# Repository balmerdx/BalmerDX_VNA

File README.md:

# BalmerDX_VNA
Vector Network Analyzer 10 KHz - 180 MHz

[See Wiki documentation for details](https://github.com/balmerdx/BalmerDX_VNA/wiki)

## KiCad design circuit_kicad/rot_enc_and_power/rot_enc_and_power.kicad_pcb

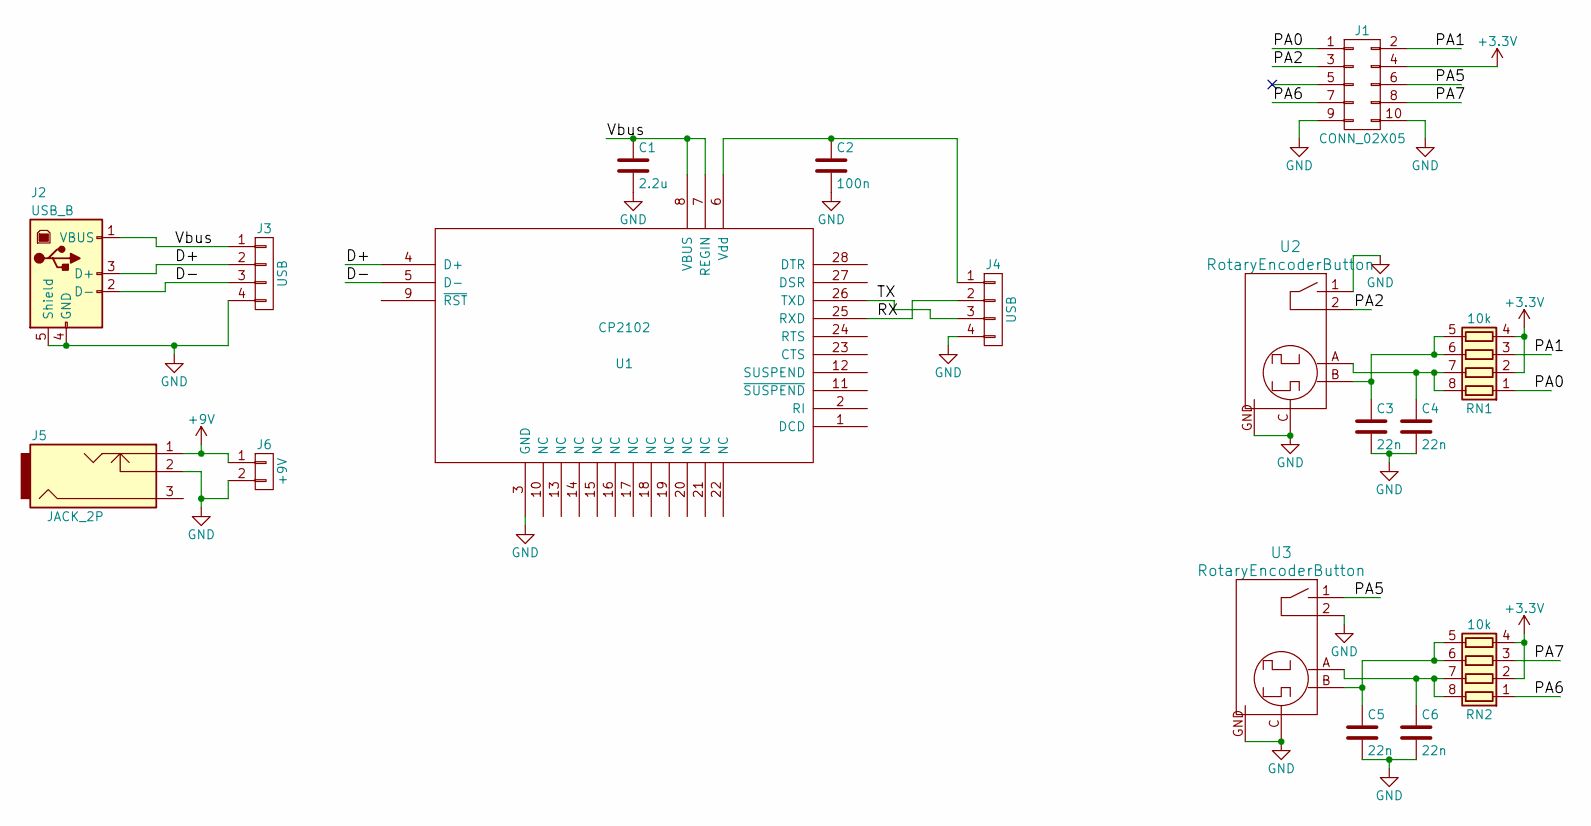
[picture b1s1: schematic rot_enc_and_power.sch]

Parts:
C1: 2.2u; C_0805
C2: 100n; C_0603
C3, C4, C5, C6: 22n; C_0603
J1: CONN_02X05; IDC_10M
J2: USB_B
J3, J4: USB; Pin_Header_Straight_1x04
J5: JACK_2P; JACK_ALIM
J6: +9V; Pin_Header_Straight_1x02
RN1, RN2: 10k; R_Array_Concave_4x0402
U1: CP2102; MLP-28
U2, U3: RotaryEncoderButton; RotEncButton

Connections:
+3V3: J1.4, RN1.2 (R2.1), RN1.4 (R4.1), RN2.2 (R2.1), RN2.4 (R4.1)
+9V: J5.1, J6.1
/D+: J2.3 (D+), J3.2, U1.4 (D+)
/D-: J2.2 (D-), J3.3, U1.5 (D-)
/PA0: J1.1, RN1.1 (R1.1)
/PA1: J1.2, RN1.3 (R3.1)
/PA2: J1.3, U2.2
/PA5: J1.6, U3.1
/PA6: J1.7, RN2.1 (R1.1)
/PA7: J1.8, RN2.3 (R3.1)
/RX: J4.2, U1.25 (RXD)
/TX: J4.3, U1.26 (TXD)
/Vbus: C1.1, J2.1 (VBUS), J3.1, U1.7 (REGIN), U1.8 (VBUS)
GND: C1.2, C2.2, C3.2, C4.2, C5.2, C6.2, J1.9, J1.10, J2.4 (GND), J2.5 (Shield), J3.4, J4.4, J5.2, J6.2, U1.3 (GND), U2.1, U2.C, U2.GND, U3.2, U3.C, U3.GND
unnamed: C2.1, J4.1, U1.6 (Vdd)
unnamed: C3.1, RN1.5 (R4.2), RN1.6 (R3.2), U2.B
unnamed: C4.1, RN1.7 (R2.2), RN1.8 (R1.2), U2.A
unnamed: C5.1, RN2.5 (R4.2), RN2.6 (R3.2), U3.B
unnamed: C6.1, RN2.7 (R2.2), RN2.8 (R1.2), U3.A

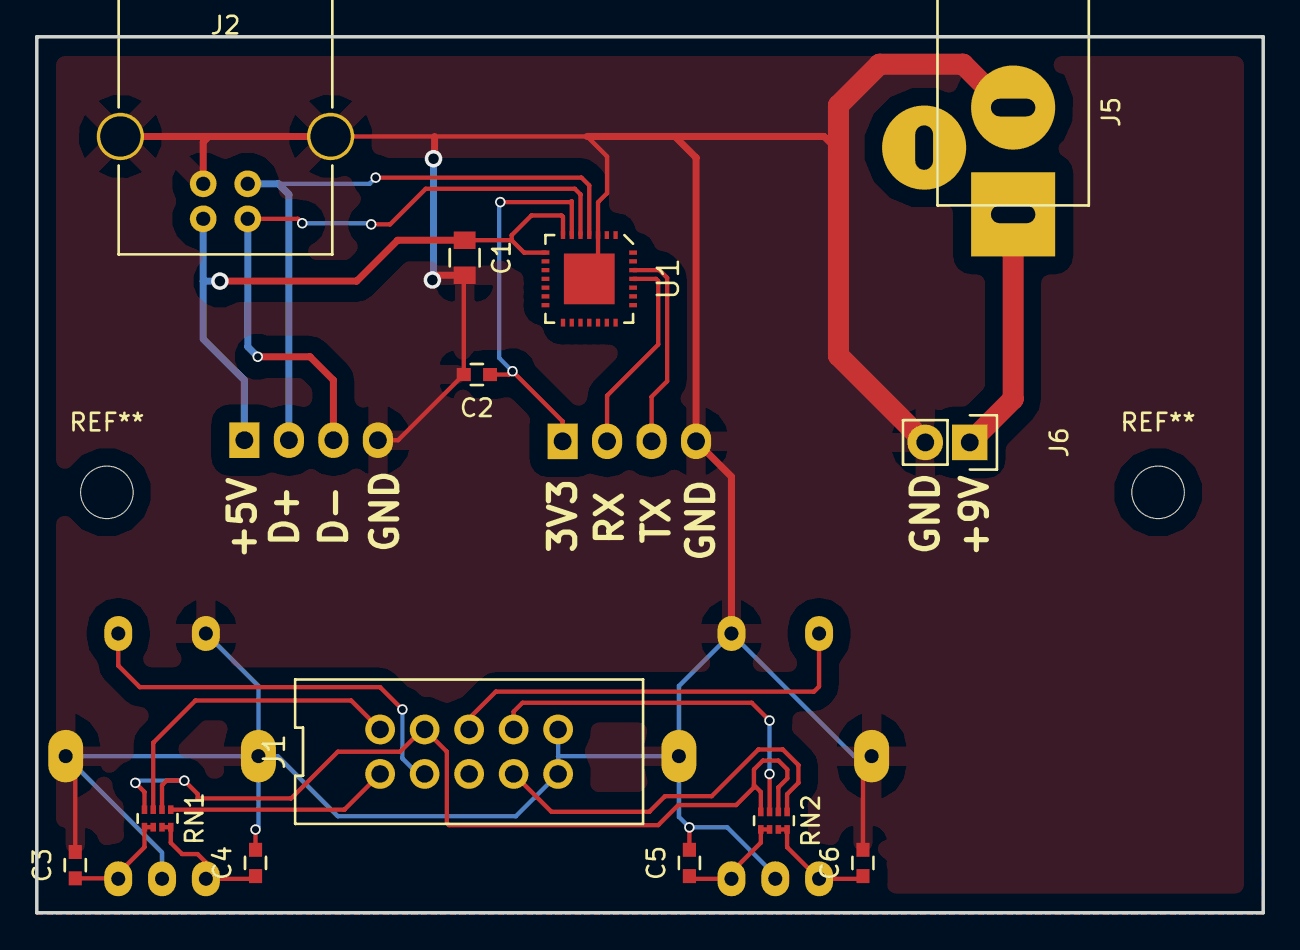
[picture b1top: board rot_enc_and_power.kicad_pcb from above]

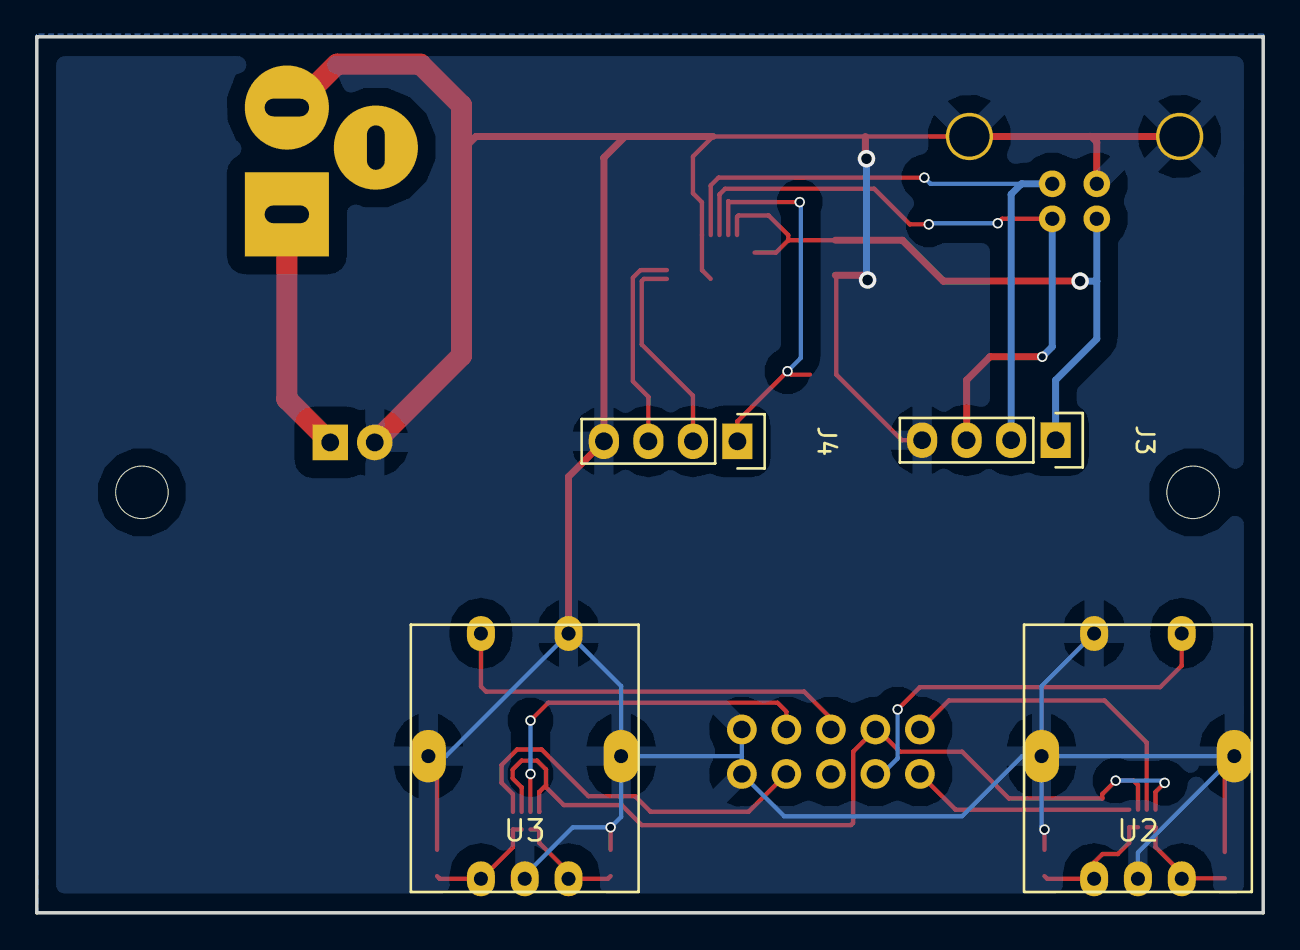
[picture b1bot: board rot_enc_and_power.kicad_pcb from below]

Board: 2 copper layers, 70.0 x 50.0 mm, 17 parts (4 on the bottom side), 19 nets.

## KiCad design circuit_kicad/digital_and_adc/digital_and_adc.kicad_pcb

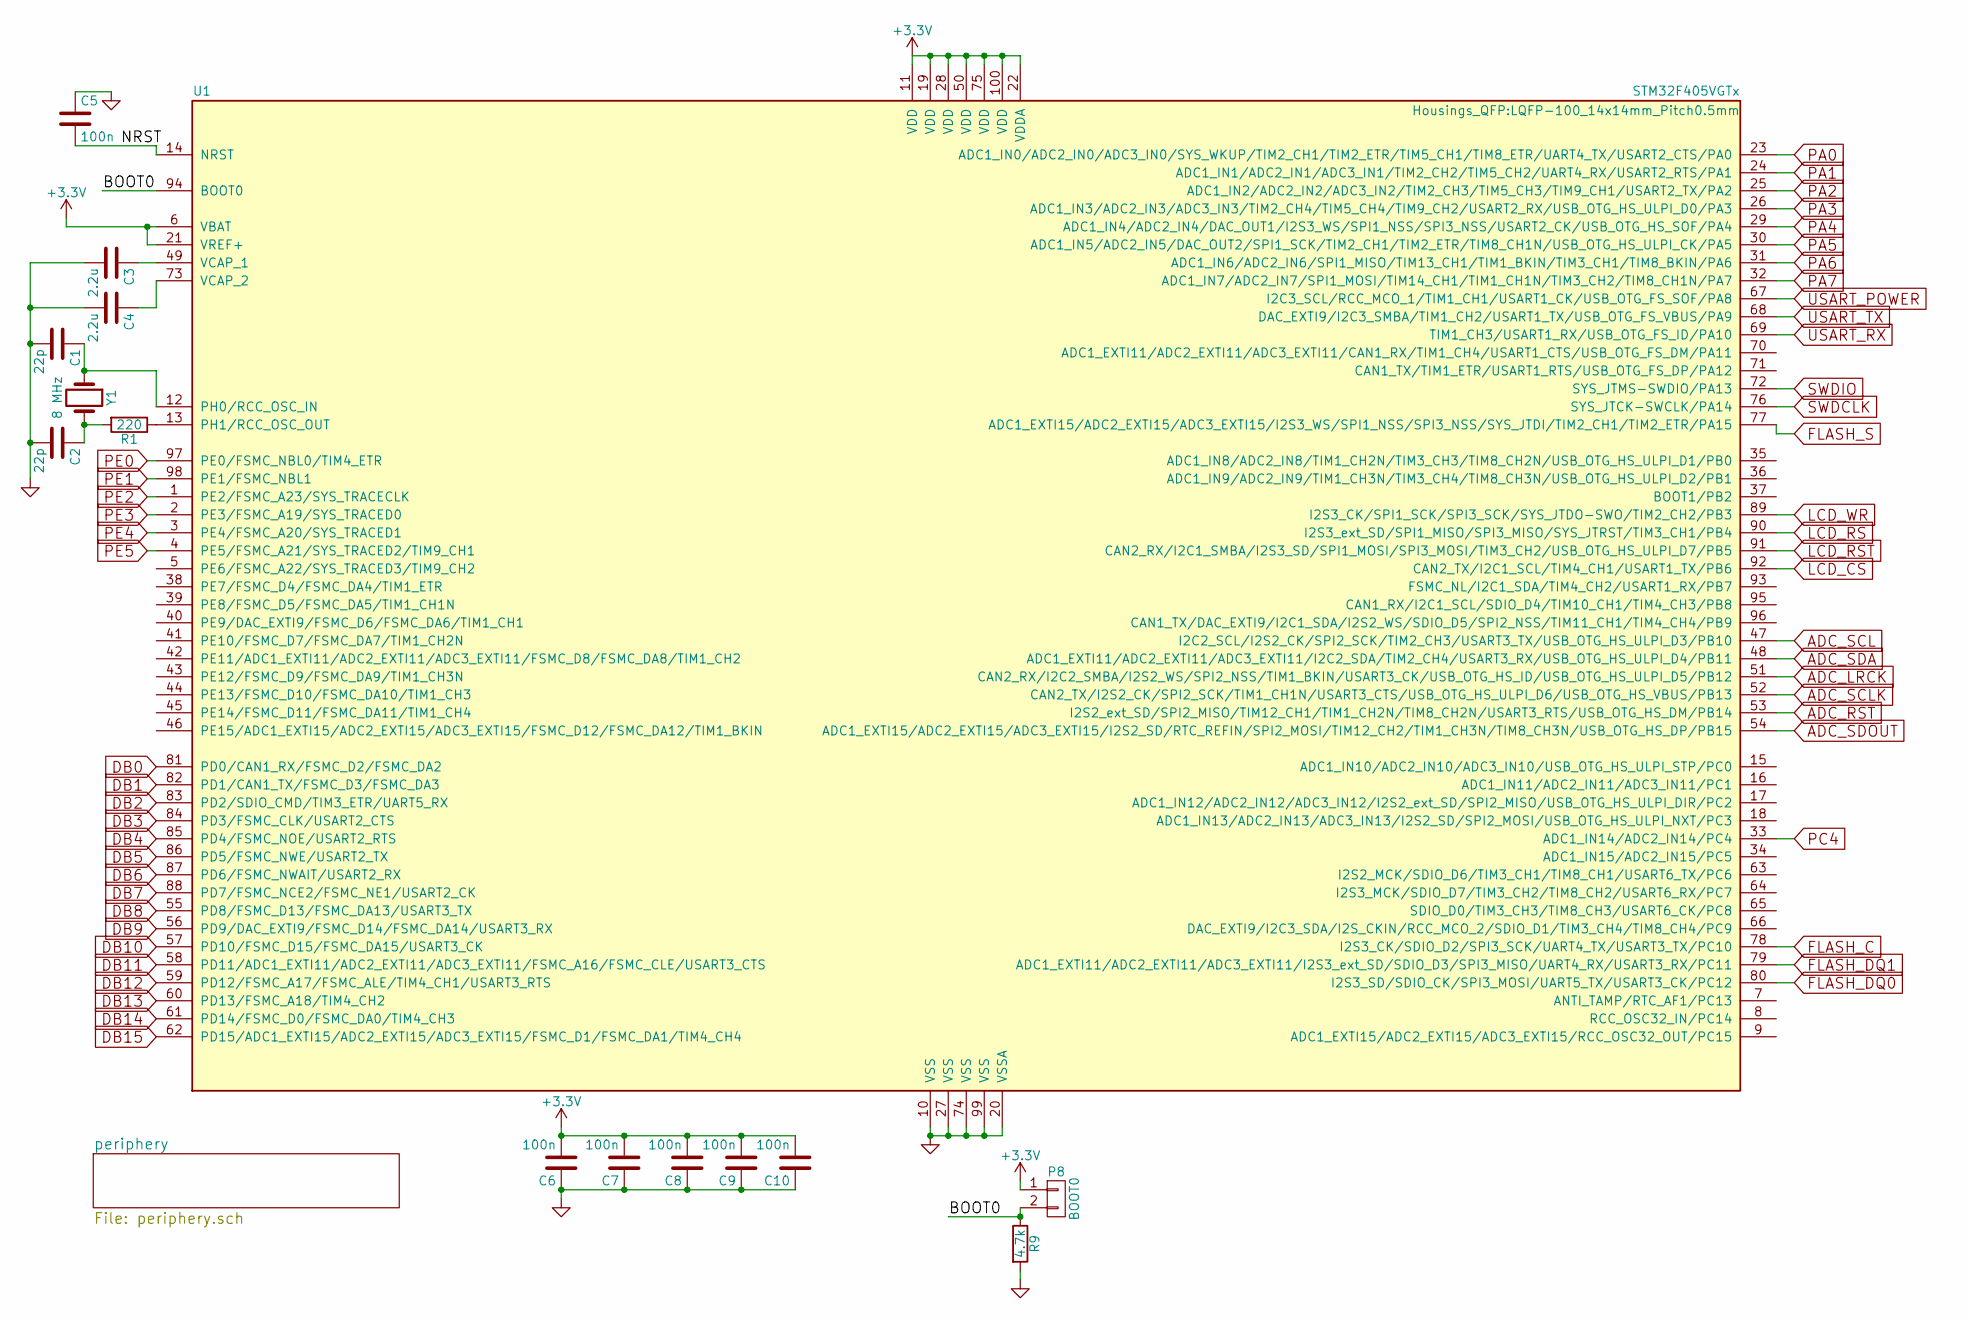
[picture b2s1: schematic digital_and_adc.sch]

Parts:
C1, C2: 22p; C_0603
C3, C4: 2.2u; C_0805
C5, C6, C7, C8, C9, C10: 100n; C_0603
P8: BOOT0; Pin_Header_Straight_1x02
R1: 220; R_0603
R9: 4.7k; R_0603
U1: STM32F405VGTx; LQFP-100_14x14mm_Pitch0.5mm
Y1: 8 MHz; Crystal_HC49-U_Vertical

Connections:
+3V3: C6.2, C7.2, C8.2, C9.2, C10.2, P8.1, U1.6 (VBAT), U1.11 (VDD), U1.19 (VDD), U1.21 (VREF+), U1.22 (VDDA), U1.28 (VDD), U1.50 (VDD), U1.75 (VDD), U1.100 (VDD); also elsewhere on the board
/BOOT0: P8.2, R9.1, U1.94 (BOOT0)
/NRST: C5.2, U1.14 (NRST)
ADC_LRCK: U1.51 (CAN2_RX/I2C2_SMBA/I2S2_WS/SPI2_NSS/TIM1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); also elsewhere on the board
ADC_RST: U1.53 (I2S2_ext_SD/SPI2_MISO/TIM12_CH1/TIM1_CH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); also elsewhere on the board
ADC_SCL: U1.47 (I2C2_SCL/I2S2_CK/SPI2_SCK/TIM2_CH3/USAR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); also elsewhere on the board
ADC_SCLK: U1.52 (CAN2_TX/I2S2_CK/SPI2_SCK/TIM1_CH1N/USAR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); also elsewhere on the board
ADC_SDA: U1.48 (ADC1_EXTI11/ADC2_EXTI11/ADC3_EXTI11/I2C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); also elsewhere on the board
ADC_SDOUT: U1.54 (ADC1_EXTI15/ADC2_EXTI15/ADC3_EXTI15/I2S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); also elsewhere on the board
DB0: U1.81 (PD0/CAN1_RX/FSMC_D2/FSMC_DA2); also elsewhere on the board
DB1: U1.82 (PD1/CAN1_TX/FSMC_D3/FSMC_DA3); also elsewhere on the board
DB2: U1.83 (PD2/SDIO_CMD/TIM3_ETR/UART5_RX); also elsewhere on the board
DB3: U1.84 (PD3/FSMC_CLK/USART2_CTS); also elsewhere on the board
DB4: U1.85 (PD4/FSMC_NOE/USART2_RTS); also elsewhere on the board
DB5: U1.86 (PD5/FSMC_NWE/USART2_TX); also elsewhere on the board
DB6: U1.87 (PD6/FSMC_NWAIT/USART2_RX); also elsewhere on the board
DB7: U1.88 (PD7/FSMC_NCE2/FSMC_NE1/USART2_CK); also elsewhere on the board
DB8: U1.55 (PD8/FSMC_D13/FSMC_DA13/USART3_TX); also elsewhere on the board
DB9: U1.56 (PD9/DAC_EXTI9/FSMC_D14/FSMC_DA14/USART3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); also elsewhere on the board
DB10: U1.57 (PD10/FSMC_D15/FSMC_DA15/USART3_CK); also elsewhere on the board
DB11: U1.58 (PD11/ADC1_EXTI11/ADC2_EXTI11/ADC3_EXTI1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); also elsewhere on the board
DB12: U1.59 (PD12/FSMC_A17/FSMC_ALE/TIM4_CH1/USART3_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); also elsewhere on the board
DB13: U1.60 (PD13/FSMC_A18/TIM4_CH2); also elsewhere on the board
DB14: U1.61 (PD14/FSMC_D0/FSMC_DA0/TIM4_CH3); also elsewhere on the board
DB15: U1.62 (PD15/ADC1_EXTI15/ADC2_EXTI15/ADC3_EXTI1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); also elsewhere on the board
FLASH_C: U1.78 (I2S3_CK/SDIO_D2/SPI3_SCK/UART4_TX/USART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); also elsewhere on the board
FLASH_DQ0: U1.80 (I2S3_SD/SDIO_CK/SPI3_MOSI/UART5_TX/USAR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); also elsewhere on the board
FLASH_DQ1: U1.79 (ADC1_EXTI11/ADC2_EXTI11/ADC3_EXTI11/I2S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); also elsewhere on the board
FLASH_S: U1.77 (ADC1_EXTI15/ADC2_EXTI15/ADC3_EXTI15/I2S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); also elsewhere on the board
GNDD: C1.2, C2.2, C3.2, C4.2, C5.1, C6.1, C7.1, C8.1, C9.1, C10.1, R9.2, U1.10 (VSS), U1.20 (VSSA), U1.27 (VSS), U1.74 (VSS), U1.99 (VSS); also elsewhere on the board
LCD_CS: U1.92 (CAN2_TX/I2C1_SCL/TIM4_CH1/USART1_TX/PB6); also elsewhere on the board
LCD_RS: U1.90 (I2S3_ext_SD/SPI1_MISO/SPI3_MISO/SYS_JTR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); also elsewhere on the board
LCD_RST: U1.91 (CAN2_RX/I2C1_SMBA/I2S3_SD/SPI1_MOSI/SPI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); also elsewhere on the board
LCD_WR: U1.89 (I2S3_CK/SPI1_SCK/SPI3_SCK/SYS_JTDO-SWO/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); also elsewhere on the board
unnamed: C1.1, U1.12 (PH0/RCC_OSC_IN), Y1.1
unnamed: C2.1, R1.2, Y1.2
unnamed: C3.1, U1.49 (VCAP_1)
unnamed: C4.1, U1.73 (VCAP_2)
unnamed: R1.1, U1.13 (PH1/RCC_OSC_OUT)
PA0: U1.23 (ADC1_IN0/ADC2_IN0/ADC3_IN0/SYS_WKUP/TIM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); also elsewhere on the board
PA1: U1.24 (ADC1_IN1/ADC2_IN1/ADC3_IN1/TIM2_CH2/TIM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); also elsewhere on the board
PA2: U1.25 (ADC1_IN2/ADC2_IN2/ADC3_IN2/TIM2_CH3/TIM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); also elsewhere on the board
PA3: U1.26 (ADC1_IN3/ADC2_IN3/ADC3_IN3/TIM2_CH4/TIM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); also elsewhere on the board
PA4: U1.29 (ADC1_IN4/ADC2_IN4/DAC_OUT1/I2S3_WS/SPI1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); also elsewhere on the board
PA5: U1.30 (ADC1_IN5/ADC2_IN5/DAC_OUT2/SPI1_SCK/TIM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); also elsewhere on the board
PA6: U1.31 (ADC1_IN6/ADC2_IN6/SPI1_MISO/TIM13_CH1/T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); also elsewhere on the board
PA7: U1.32 (ADC1_IN7/ADC2_IN7/SPI1_MOSI/TIM14_CH1/T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); also elsewhere on the board
PC4: U1.33 (ADC1_IN14/ADC2_IN14/PC4); also elsewhere on the board
PE0: U1.97 (PE0/FSMC_NBL0/TIM4_ETR); also elsewhere on the board
PE1: U1.98 (PE1/FSMC_NBL1); also elsewhere on the board
PE2: U1.1 (PE2/FSMC_A23/SYS_TRACECLK); also elsewhere on the board
PE3: U1.2 (PE3/FSMC_A19/SYS_TRACED0); also elsewhere on the board
PE4: U1.3 (PE4/FSMC_A20/SYS_TRACED1); also elsewhere on the board
PE5: U1.4 (PE5/FSMC_A21/SYS_TRACED2/TIM9_CH1); also elsewhere on the board
SWDCLK: U1.76 (SYS_JTCK-SWCLK/PA14); also elsewhere on the board
SWDIO: U1.72 (SYS_JTMS-SWDIO/PA13); also elsewhere on the board
USART_POWER: U1.67 (I2C3_SCL/RCC_MCO_1/TIM1_CH1/USART1_CK/U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); also elsewhere on the board
USART_RX: U1.69 (TIM1_CH3/USART1_RX/USB_OTG_FS_ID/PA10); also elsewhere on the board
USART_TX: U1.68 (DAC_EXTI9/I2C3_SMBA/TIM1_CH2/USART1_TX/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); also elsewhere on the board

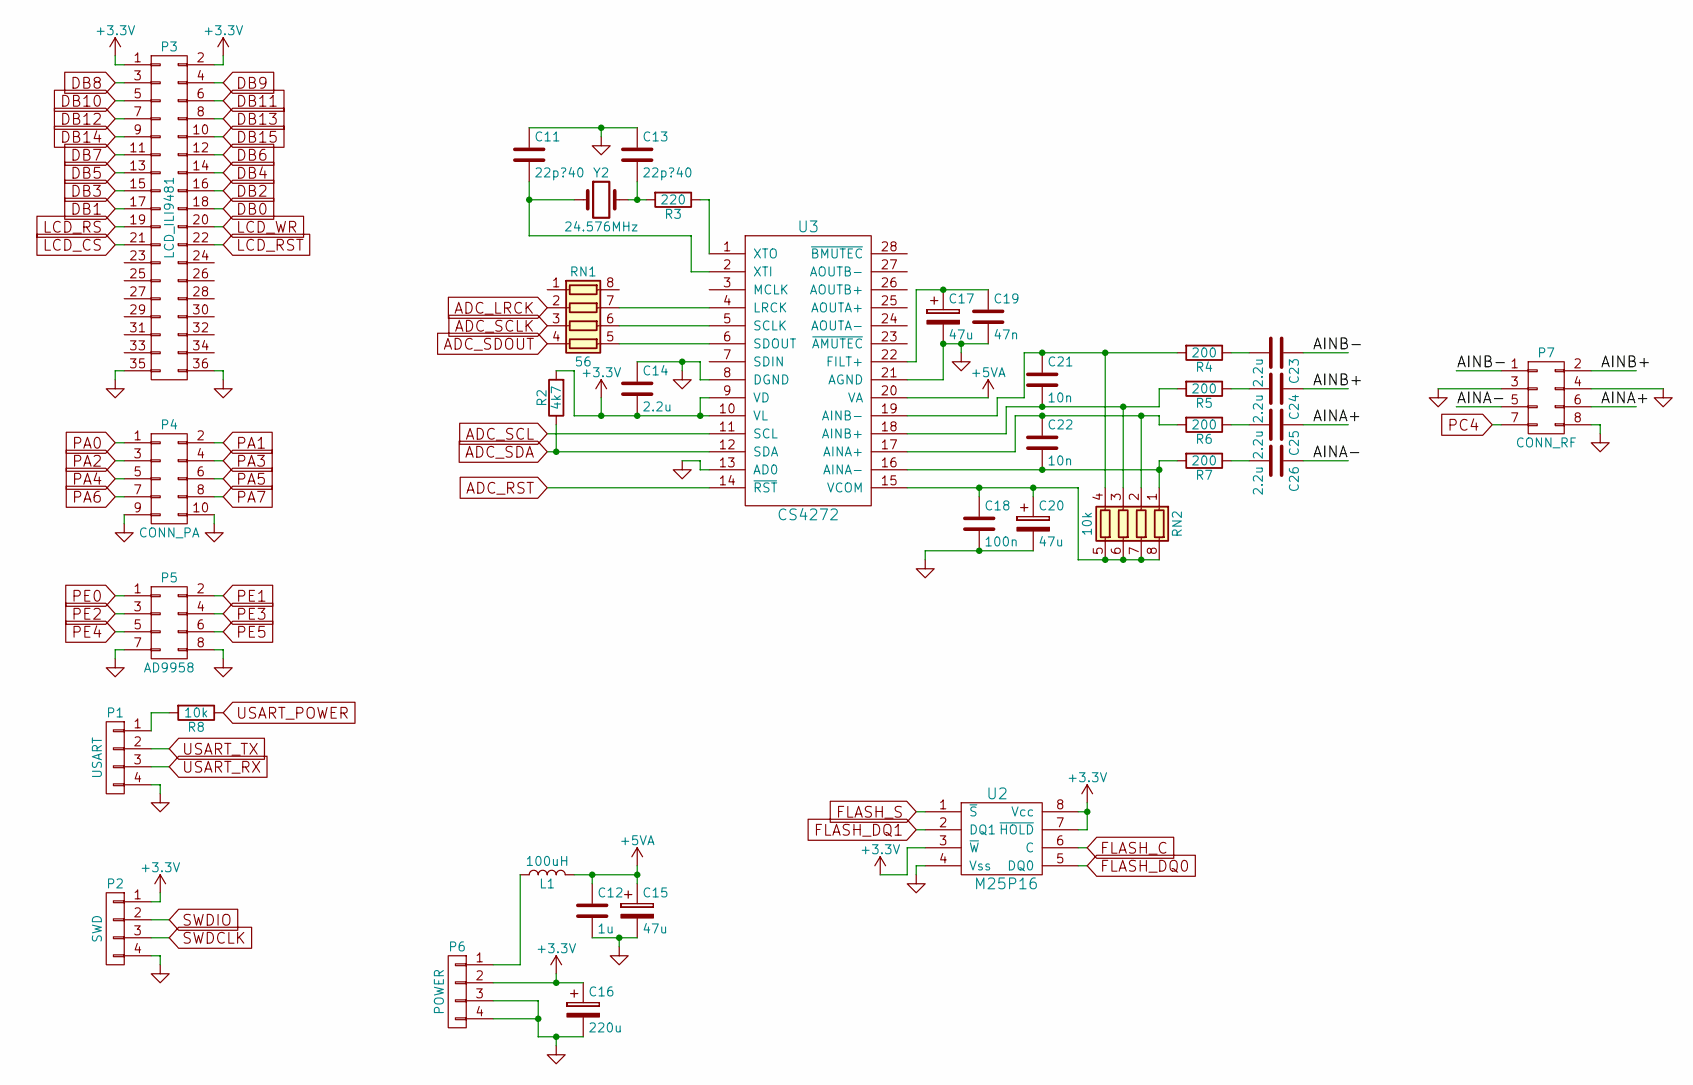
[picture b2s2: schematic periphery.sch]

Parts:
C11, C13: 22p?40; C_0603
C12: 1u; C_0805
C14, C23, C24, C25, C26: 2.2u; C_0805
C15, C17, C20: 47u; TantalC_SizeB_EIA-3528_HandSoldering
C16: 220u; c_elec_6.3x4.5
C18: 100n; C_0805
C19: 47n; C_0805
C21, C22: 10n; C_0603
L1: 100uH; Resistor_Horizontal_RM10mm
P1: USART; Pin_Header_Straight_1x04
P2: SWD; Pin_Header_Straight_1x04
P3: LCD_ILI9481; Pin_Header_Straight_2x18
P4: CONN_PA; Pin_Header_Straight_2x05
P5: AD9958; Pin_Header_Straight_2x04
P6: POWER; Pin_Header_Straight_1x04
P7: CONN_RF; Pin_Header_Straight_2x04
R2: 4k7; R_0603
R3: 220; R_0603
R4, R5, R6, R7: 200; R_0603
R8: 10k; R_0603
RN1: 56; R_Array_Concave_4x0402
RN2: 10k; R_Array_Concave_4x0402
U2: M25P16; SOIC-8-N
U3: CS4272; TSSOP-28_4.4x9.7mm_Pitch0.65mm
Y2: 24.576MHz; Crystal_HC49-U_Vertical

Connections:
+3V3: C14.2, C16.1, P2.1, P3.1, P3.2, P6.2, R2.2, U2.3 (~W), U2.7 (~HOLD), U2.8 (Vcc), U3.9 (VD), U3.10 (VL); also elsewhere on the board
+5VA: C12.1, C15.1, L1.2, U3.20 (VA)
/periphery/AINA+: C25.1, P7.6
/periphery/AINA-: C26.1, P7.5
/periphery/AINB+: C24.1, P7.2
/periphery/AINB-: C23.1, P7.1
ADC_LRCK: RN1.2 (R2.1); also elsewhere on the board
ADC_RST: U3.14 (~RST); also elsewhere on the board
ADC_SCL: U3.11 (SCL); also elsewhere on the board
ADC_SCLK: RN1.3 (R3.1); also elsewhere on the board
ADC_SDA: R2.1, U3.12 (SDA); also elsewhere on the board
ADC_SDOUT: RN1.4 (R4.1); also elsewhere on the board
DB0: P3.18; also elsewhere on the board
DB1: P3.17; also elsewhere on the board
DB2: P3.16; also elsewhere on the board
DB3: P3.15; also elsewhere on the board
DB4: P3.14; also elsewhere on the board
DB5: P3.13; also elsewhere on the board
DB6: P3.12; also elsewhere on the board
DB7: P3.11; also elsewhere on the board
DB8: P3.3; also elsewhere on the board
DB9: P3.4; also elsewhere on the board
DB10: P3.5; also elsewhere on the board
DB11: P3.6; also elsewhere on the board
DB12: P3.7; also elsewhere on the board
DB13: P3.8; also elsewhere on the board
DB14: P3.9; also elsewhere on the board
DB15: P3.10; also elsewhere on the board
FLASH_C: U2.6 (C); also elsewhere on the board
FLASH_DQ0: U2.5 (DQ0); also elsewhere on the board
FLASH_DQ1: U2.2 (DQ1); also elsewhere on the board
FLASH_S: U2.1 (~S); also elsewhere on the board
GNDD: C11.1, C12.2, C13.1, C14.1, C15.2, C16.2, C17.2, C18.2, C19.2, C20.2, P1.4, P2.4, P3.35, P3.36, P4.9, P4.10, P5.7, P5.8, P6.3, P6.4, P7.3, P7.4, P7.8, U2.4 (Vss), U3.8 (DGND), U3.13 (AD0), U3.21 (AGND); also elsewhere on the board
LCD_CS: P3.21; also elsewhere on the board
LCD_RS: P3.19; also elsewhere on the board
LCD_RST: P3.22; also elsewhere on the board
LCD_WR: P3.20; also elsewhere on the board
unnamed: C11.2, U3.2 (XTI), Y2.1
unnamed: C13.2, R3.2, Y2.2
unnamed: C17.1, C19.1, U3.22 (FILT+)
unnamed: C18.1, C20.1, RN2.5 (R4.2), RN2.6 (R3.2), RN2.7 (R2.2), RN2.8 (R1.2), U3.15 (VCOM)
unnamed: C21.1, R4.2, RN2.4 (R4.1), U3.19 (AINB-)
unnamed: C21.2, R5.2, RN2.3 (R3.1), U3.18 (AINB+)
unnamed: C22.1, R6.2, RN2.2 (R2.1), U3.17 (AINA+)
unnamed: C22.2, R7.2, RN2.1 (R1.1), U3.16 (AINA-)
unnamed: C23.2, R4.1
unnamed: C24.2, R5.1
unnamed: C25.2, R6.1
unnamed: C26.2, R7.1
unnamed: L1.1, P6.1
unnamed: P1.1, R8.2
unnamed: R3.1, U3.1 (XTO)
unnamed: RN1.5 (R4.2), U3.6 (SDOUT)
unnamed: RN1.6 (R3.2), U3.5 (SCLK)
unnamed: RN1.7 (R2.2), U3.4 (LRCK)
PA0: P4.1; also elsewhere on the board
PA1: P4.2; also elsewhere on the board
PA2: P4.3; also elsewhere on the board
PA3: P4.4; also elsewhere on the board
PA4: P4.5; also elsewhere on the board
PA5: P4.6; also elsewhere on the board
PA6: P4.7; also elsewhere on the board
PA7: P4.8; also elsewhere on the board
PC4: P7.7; also elsewhere on the board
PE0: P5.1; also elsewhere on the board
PE1: P5.2; also elsewhere on the board
PE2: P5.3; also elsewhere on the board
PE3: P5.4; also elsewhere on the board
PE4: P5.5; also elsewhere on the board
PE5: P5.6; also elsewhere on the board
SWDCLK: P2.3; also elsewhere on the board
SWDIO: P2.2; also elsewhere on the board
USART_POWER: R8.1; also elsewhere on the board
USART_RX: P1.3; also elsewhere on the board
USART_TX: P1.2; also elsewhere on the board

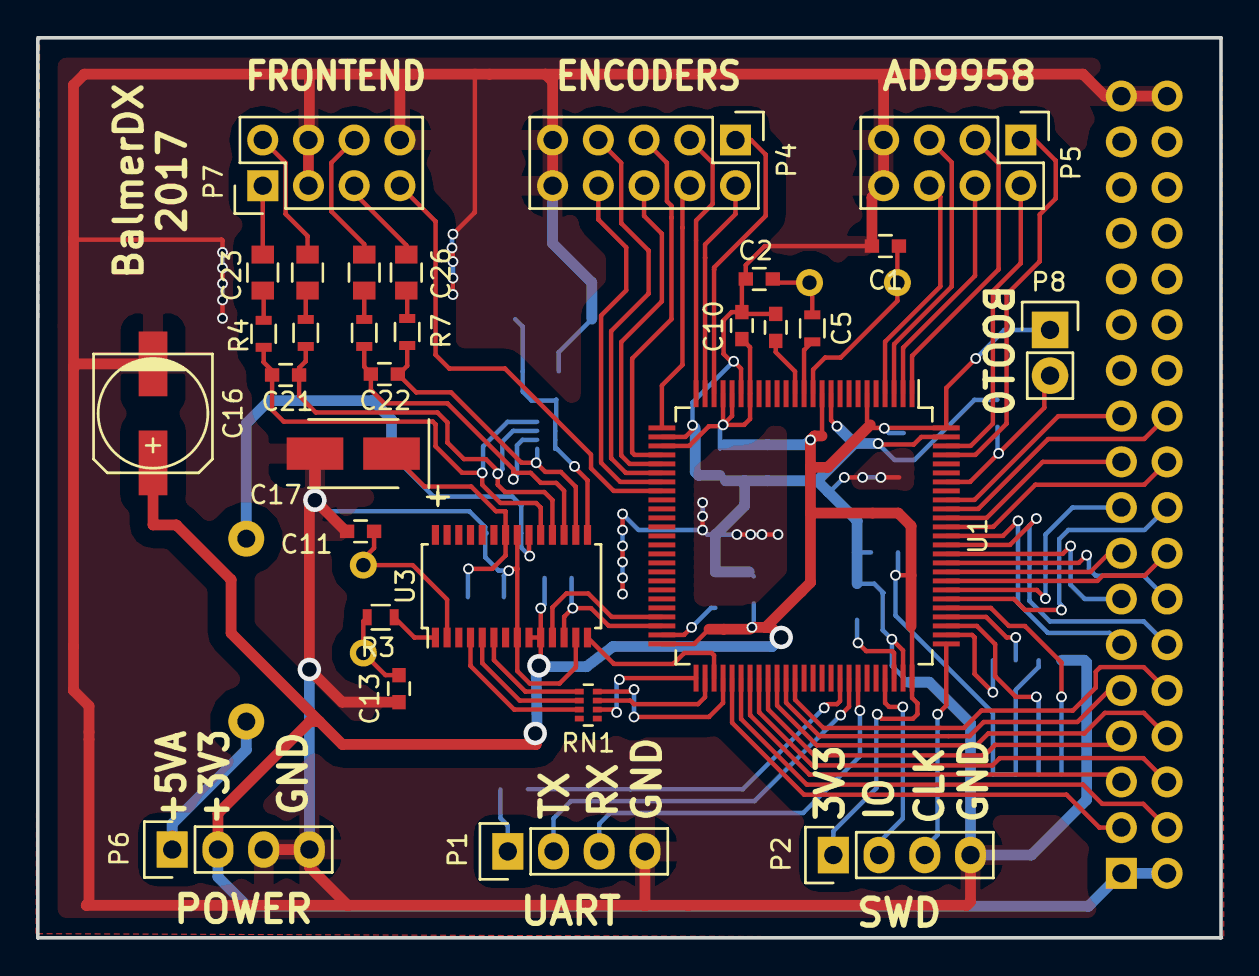
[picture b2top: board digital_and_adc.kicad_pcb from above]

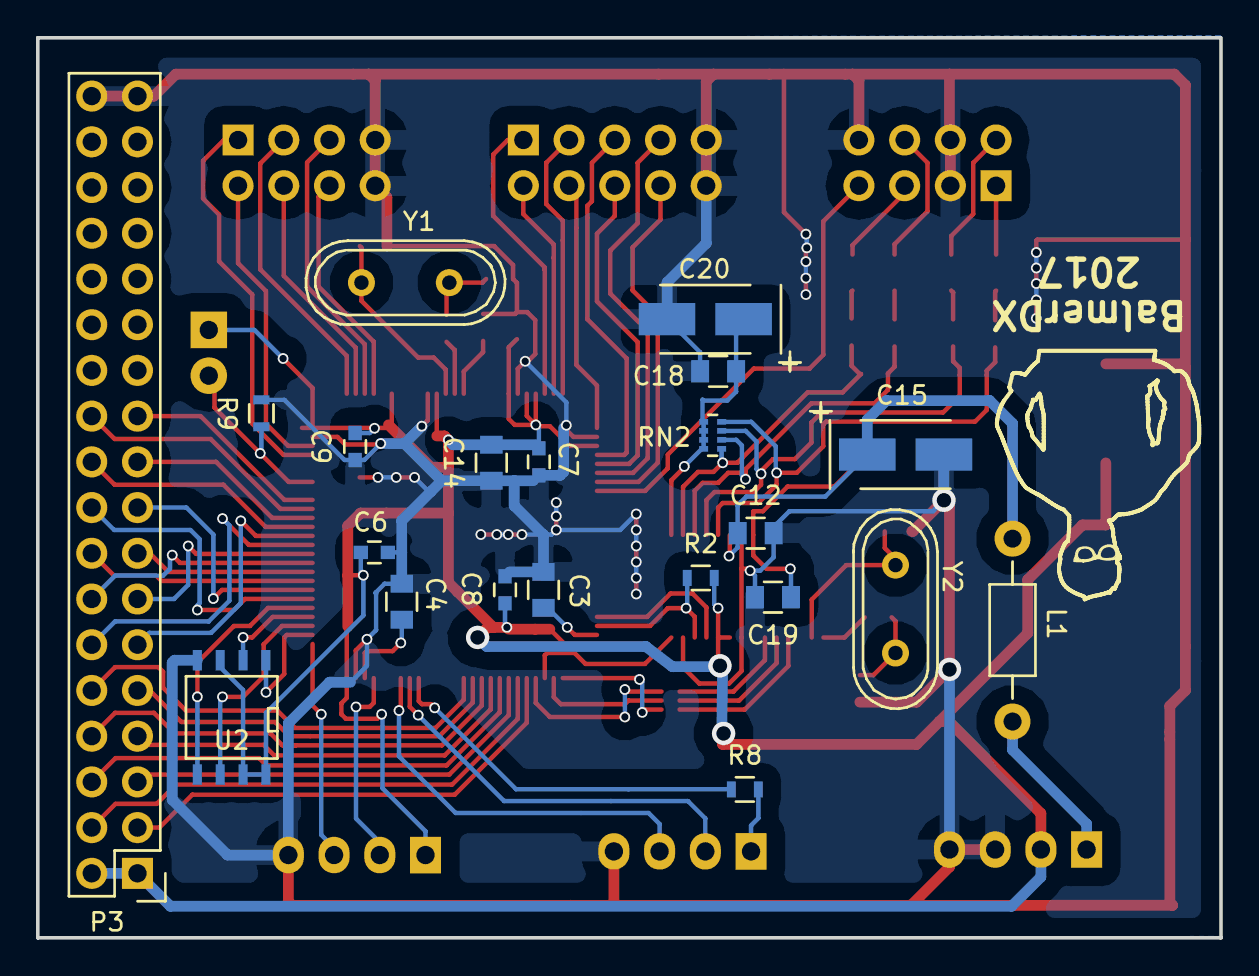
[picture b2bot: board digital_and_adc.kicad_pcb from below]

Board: 2 copper layers, 65.7 x 50.0 mm, 52 parts (22 on the bottom side), 82 nets.

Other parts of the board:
balmer_logo: balmer; balmer_logo

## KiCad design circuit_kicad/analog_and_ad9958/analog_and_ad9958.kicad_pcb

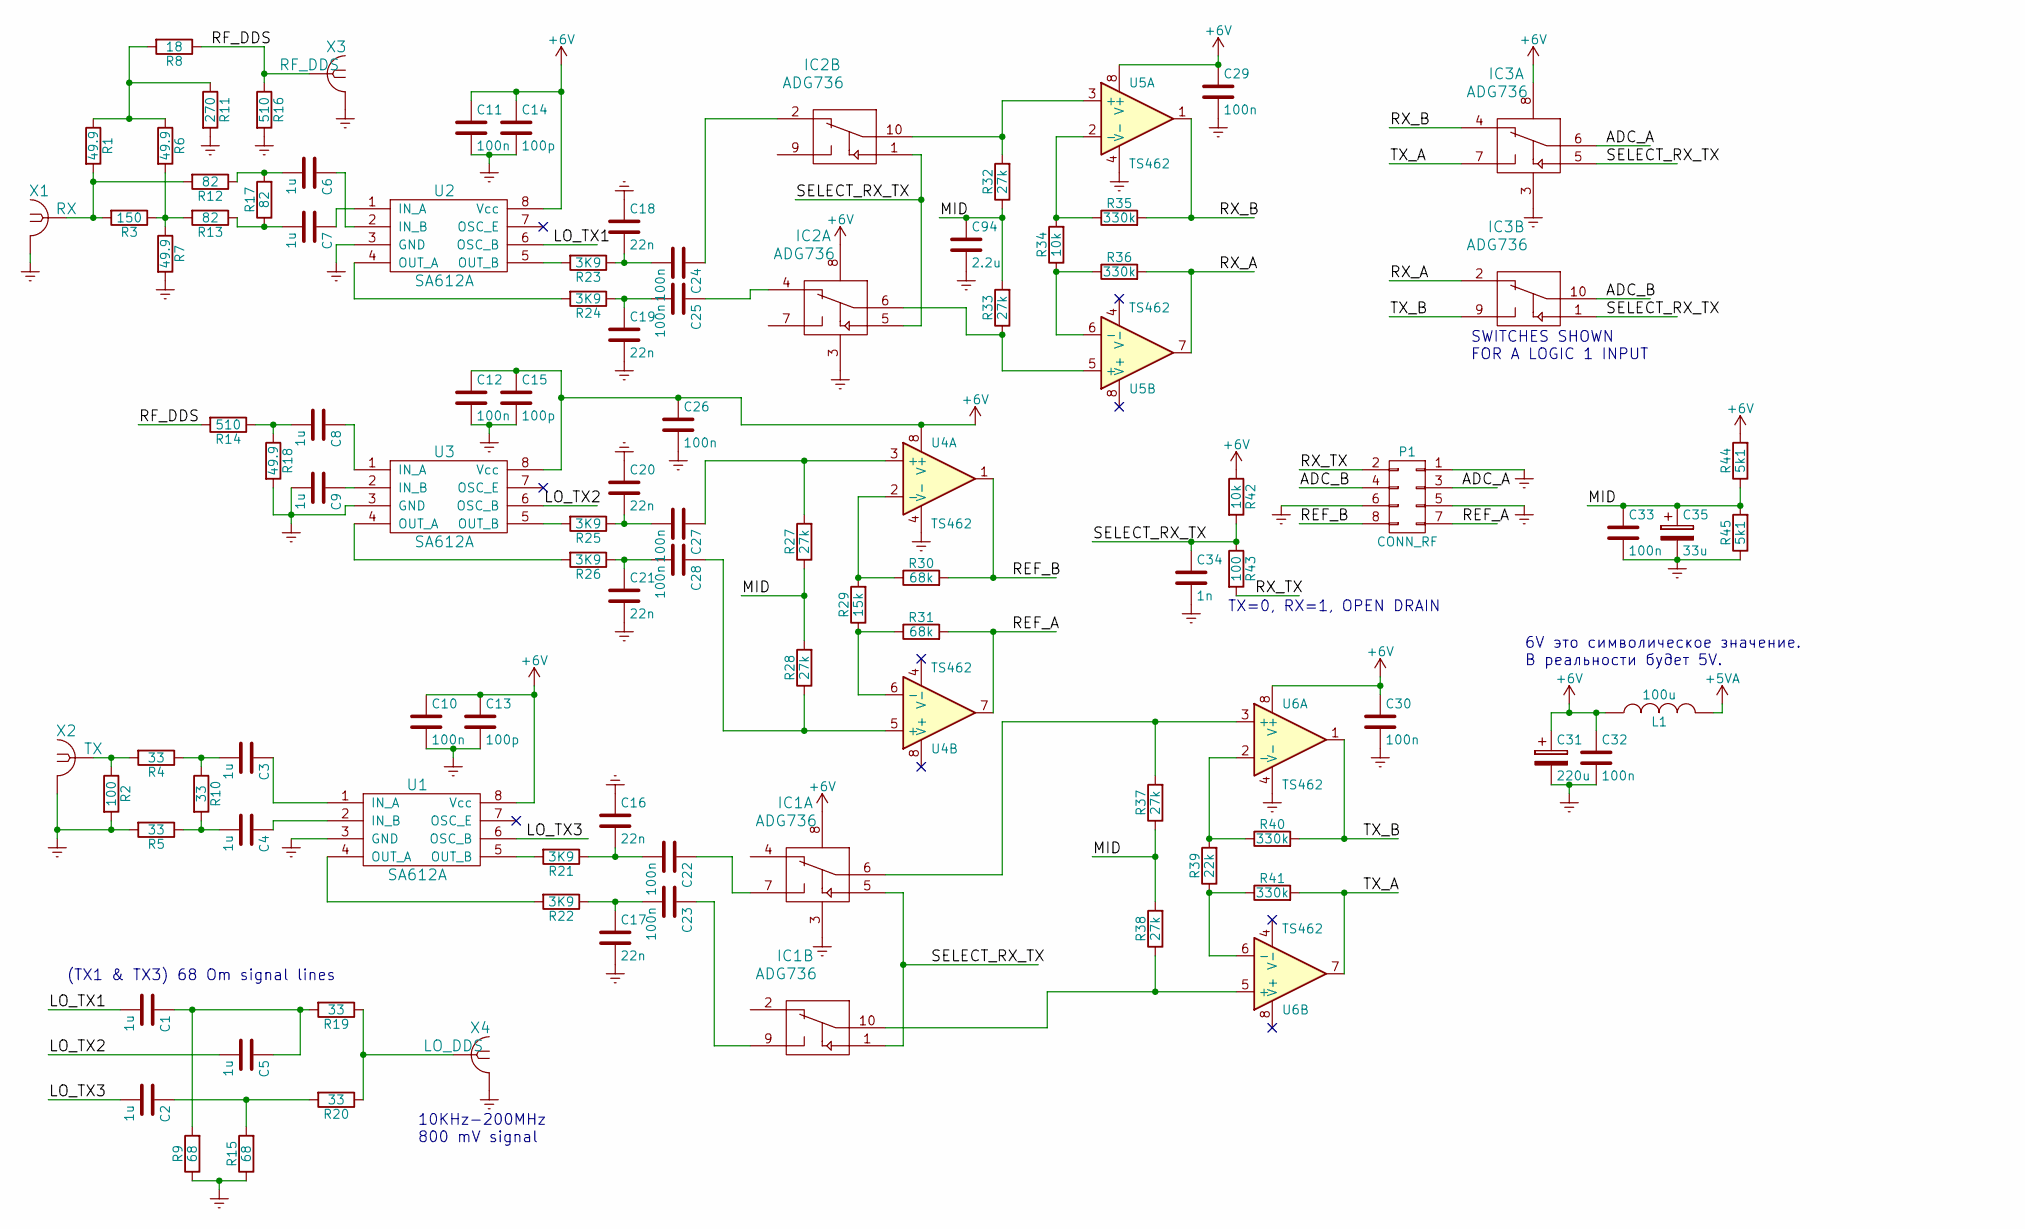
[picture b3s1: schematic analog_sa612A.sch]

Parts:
C1, C2, C3, C4, C5, C6, C7, C8, C9: 1u; C_0603
C10, C11, C12, C22, C23, C24, C25, C26, C27, C28, C29, C30, C32, C33: 100n; C_0603
C13, C14, C15: 100p; C_0603
C16, C17, C18, C19, C20, C21: 22n; C_0603
C31: 220u; c_elec_6.3x4.5
C34: 1n; C_0603
C35: 33u; c_elec_6.3x4.5
C94: 2.2u; C_0805
IC1, IC2, IC3: ADG736; MSOP-10_3x3mm_Pitch0.5mm
L1: 100u; Resistor_Horizontal_RM10mm
P1: CONN_RF; IDC_08M
R1, R6, R7, R18: 49.9; R_0603
R2, R43: 100; R_0603
R3: 150; R_0603
R4, R5, R10: 33; R_0603
R8: 18; R_0603
R9, R15: 68; R_0805
R11: 270; R_0603
R12, R13, R17: 82; R_0603
R14, R16: 510; R_0603
R19, R20: 33; R_0805
R21, R22, R23, R24, R25, R26: 3K9; R_0603
R27, R28, R32, R33, R37, R38: 27k; R_0603
R29: 15k; R_0603
R30, R31: 68k; R_0603
R34, R42: 10k; R_0603
R35, R36, R40, R41: 330k; R_0603
R39: 22k; R_0603
R44, R45: 5k1; R_0603
U1, U2, U3: SA612A; SOIC-8-N
U4, U5, U6: TS462; SOIC-8-N
X1: RX; SMA-NORMAL
X2: TX; SMA-NORMAL
X3: RF_DDS; SMA-NORMAL-MY
X4: LO_DDS; SMA-NORMAL-MY

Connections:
+5VA: L1.2; also elsewhere on the board
+6V: C10.1, C11.1, C12.1, C13.1, C14.1, C15.1, C26.1, C29.1, C30.1, C31.1, C32.1, IC1.8, IC2.8, IC3.8, L1.1, R42.1, R44.2, U1.8 (Vcc), U2.8 (Vcc), U3.8 (Vcc), U4.8 (V+), U5.8 (V+), U6.8 (V+)
/analog_sa612A/ADC_A: IC3.6, P1.3
/analog_sa612A/ADC_B: IC3.10, P1.4
/analog_sa612A/LO_TX1: C1.2, U2.6 (OSC_B)
/analog_sa612A/LO_TX2: C5.2, U3.6 (OSC_B)
/analog_sa612A/LO_TX3: C2.2, U1.6 (OSC_B)
/analog_sa612A/MID: C33.1, C35.1, C94.1, R27.1, R28.2, R32.1, R33.2, R37.1, R38.2, R44.1, R45.2
/analog_sa612A/REF_A: P1.7, R31.2, U4.7
/analog_sa612A/REF_B: P1.8, R30.2, U4.1
/analog_sa612A/RF_DDS: R8.1, R14.2, R16.1, X3.1
/analog_sa612A/RX_A: IC3.2, R36.2, U5.7
/analog_sa612A/RX_B: IC3.4, R35.2, U5.1
/analog_sa612A/RX_TX: P1.2, R43.2
/analog_sa612A/SELECT_RX_TX: C34.1, IC1.1, IC1.5, IC2.1, IC2.5, IC3.1, IC3.5, R42.2, R43.1
/analog_sa612A/TX_A: IC3.7, R41.2, U6.7
/analog_sa612A/TX_B: IC3.9, R40.2, U6.1
Earth: C9.2, C10.2, C11.2, C12.2, C13.2, C14.2, C15.2, C16.1, C17.2, C18.1, C19.2, C20.1, C21.2, C26.2, C29.2, C30.2, C31.2, C32.2, C33.2, C34.2, C35.2, C94.2, IC1.3, IC2.3, IC3.3, P1.1, P1.5, P1.6, R2.2, R5.2, R7.2, R9.1, R11.2, R15.1, R16.2, R18.2, R45.1, U1.3 (GND), U2.3 (GND), U3.3 (GND), U4.4 (V-), U5.4 (V-), U6.4 (V-), X1.2 (GND), X2.2 (GND), X3.2 (GND), X4.2 (GND); also elsewhere on the board
unnamed: C1.1, C5.1, R9.2, R19.2
unnamed: C2.1, R15.2, R20.2
unnamed: C3.1, U1.1 (IN_A)
unnamed: C3.2, R4.1, R10.1
unnamed: C4.1, U1.2 (IN_B)
unnamed: C4.2, R5.1, R10.2
unnamed: C6.1, U2.2 (IN_B)
unnamed: C6.2, R12.1, R17.2
unnamed: C7.1, U2.1 (IN_A)
unnamed: C7.2, R13.1, R17.1
unnamed: C8.1, U3.1 (IN_A)
unnamed: C8.2, R14.1, R18.1
unnamed: C9.1, U3.2 (IN_B)
unnamed: C16.2, C22.2, R21.1
unnamed: C17.1, C23.2, R22.1
unnamed: C18.2, C24.2, R23.1
unnamed: C19.1, C25.2, R24.1
unnamed: C20.2, C27.2, R25.1
unnamed: C21.1, C28.2, R26.1
unnamed: C22.1, IC1.7
unnamed: C23.1, IC1.9
unnamed: C24.1, IC2.2
unnamed: C25.1, IC2.4
unnamed: C27.1, R27.2, U4.3 (+)
unnamed: C28.1, R28.1, U4.5 (+)
unnamed: IC1.6, R37.2, U6.3 (+)
unnamed: IC1.10, R38.1, U6.5 (+)
unnamed: IC2.6, R33.1, U5.5 (+)
unnamed: IC2.10, R32.2, U5.3 (+)
unnamed: R1.1, R6.1, R8.2, R11.1
unnamed: R1.2, R3.2, R12.2, X1.1
unnamed: R2.1, R4.2, X2.1
unnamed: R3.1, R6.2, R7.1, R13.2
unnamed: R19.1, R20.1, X4.1
unnamed: R21.2, U1.5 (OUT_B)
unnamed: R22.2, U1.4 (OUT_A)
unnamed: R23.2, U2.5 (OUT_B)
unnamed: R24.2, U2.4 (OUT_A)
unnamed: R25.2, U3.5 (OUT_B)
unnamed: R26.2, U3.4 (OUT_A)
unnamed: R29.1, R31.1, U4.6 (-)
unnamed: R29.2, R30.1, U4.2 (-)
unnamed: R34.1, R36.1, U5.6 (-)
unnamed: R34.2, R35.1, U5.2 (-)
unnamed: R39.1, R41.1, U6.6 (-)
unnamed: R39.2, R40.1, U6.2 (-)

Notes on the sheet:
SWITCHES SHOWN FOR A LOGIC 1 INPUT
TX=0, RX=1, OPEN DRAIN
(TX1 & TX3) 68 Om signal lines
10KHz-200MHz 800 mV signal
6V это символическое значение. В реальности будет 5V.
